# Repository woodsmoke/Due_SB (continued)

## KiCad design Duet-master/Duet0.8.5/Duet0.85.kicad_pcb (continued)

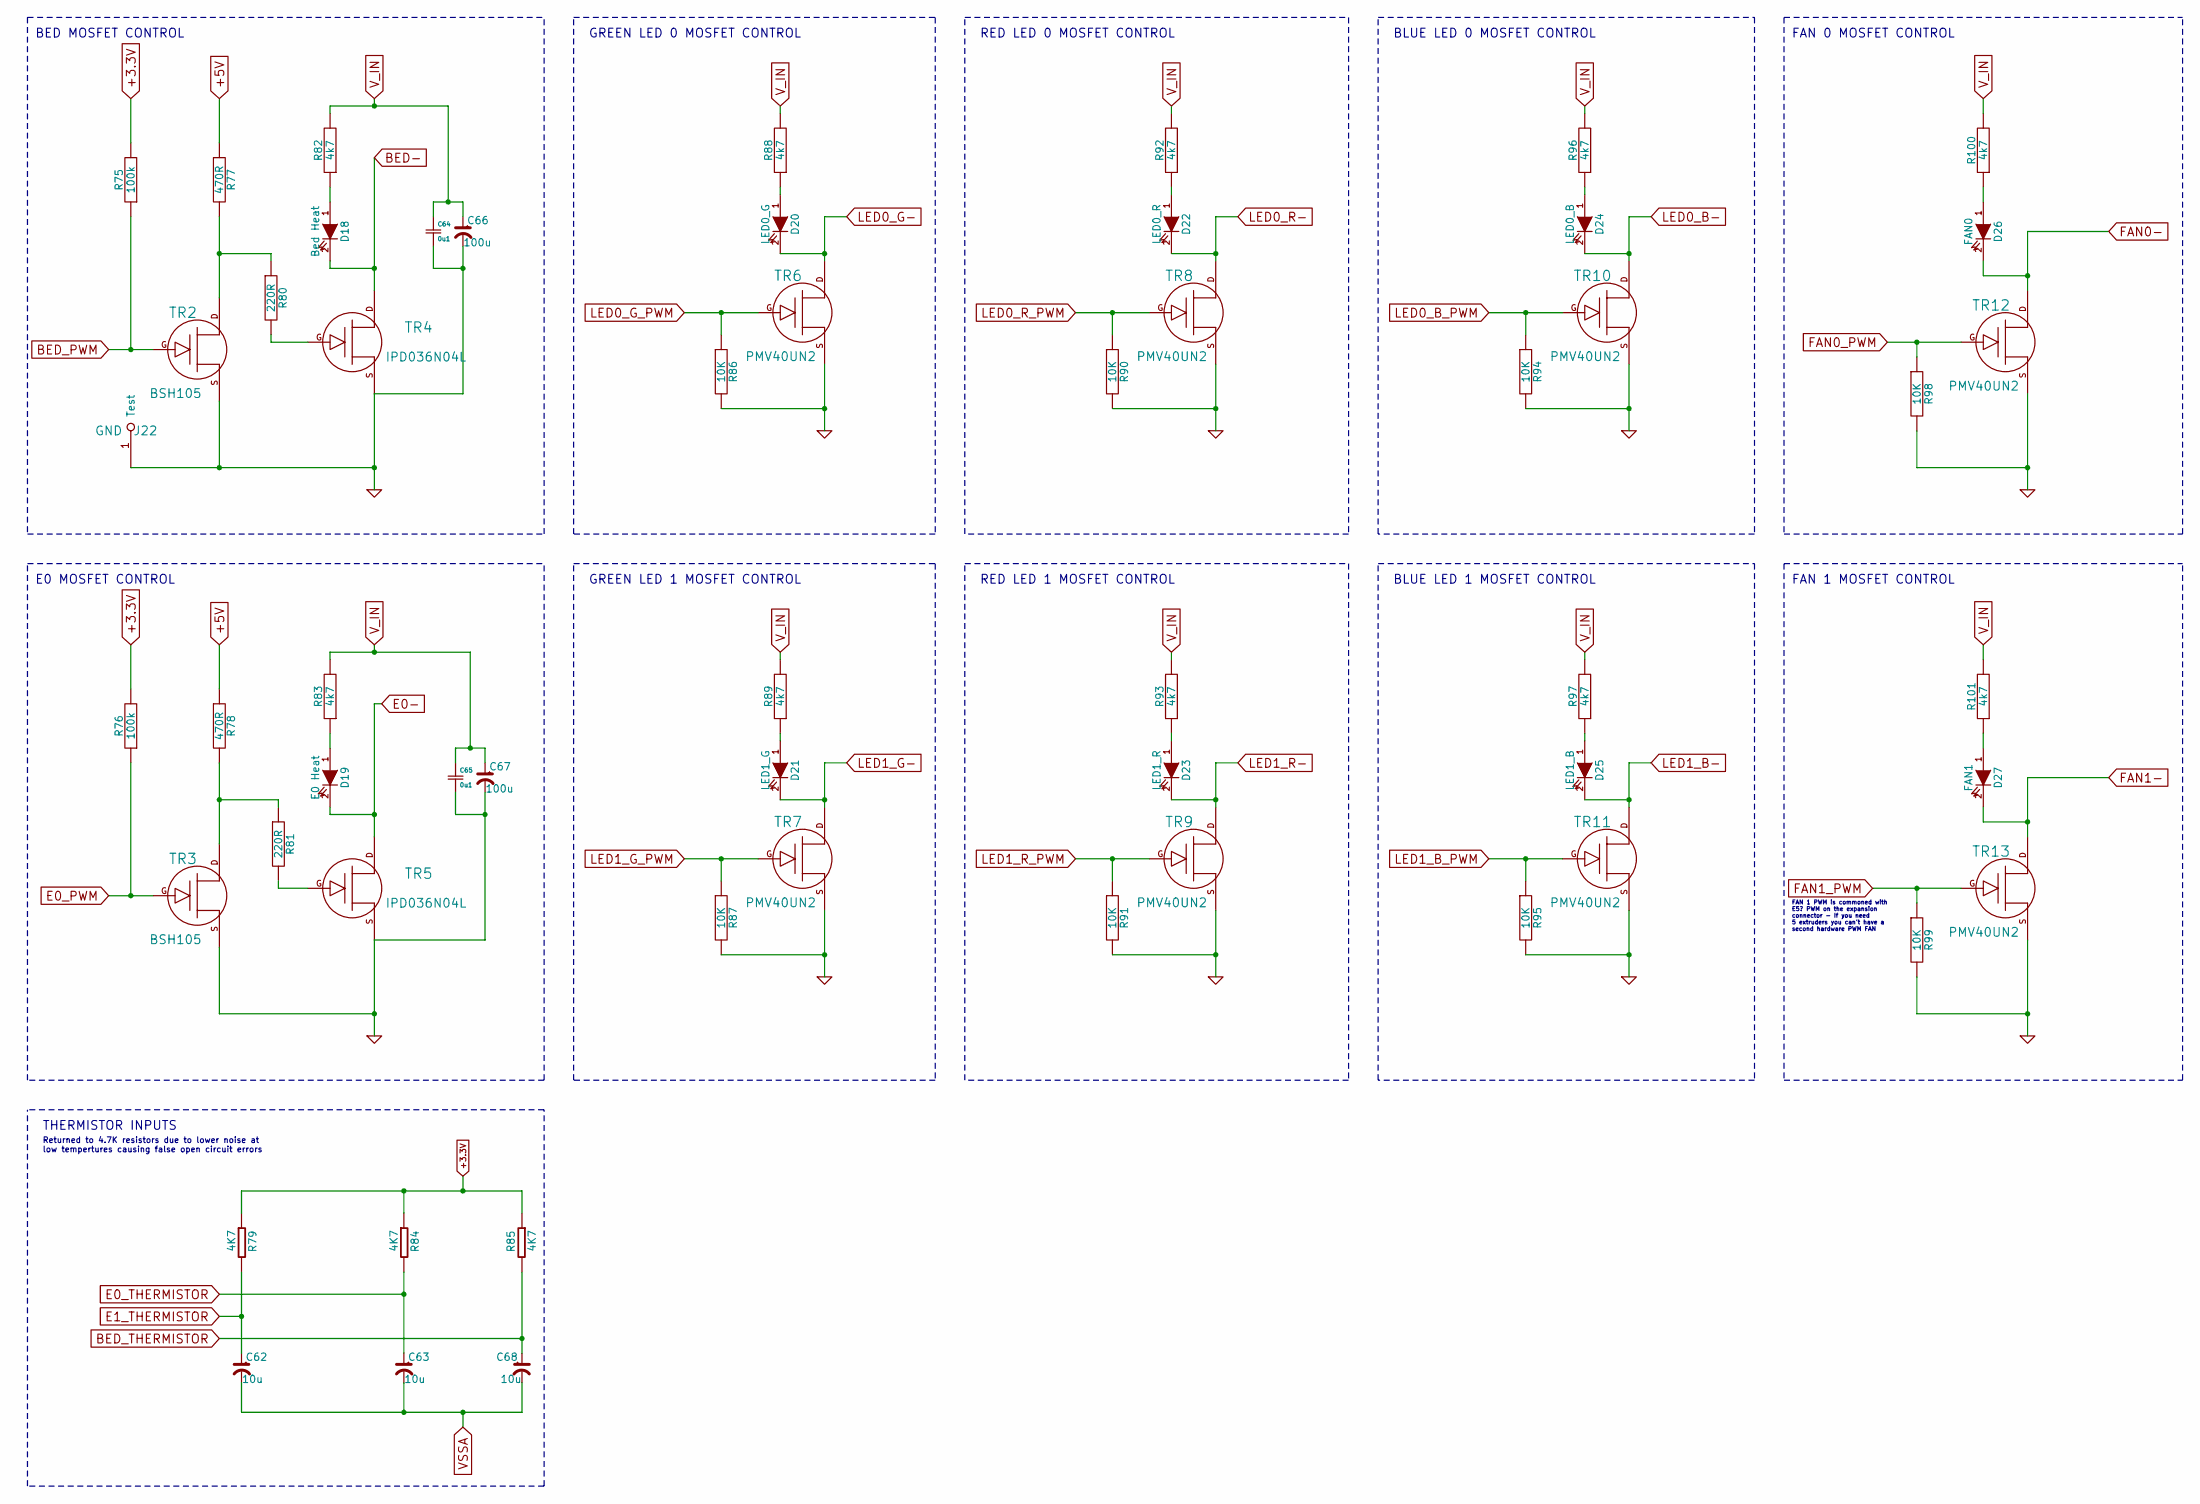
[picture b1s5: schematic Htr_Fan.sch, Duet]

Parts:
C62, C63, C68: 10u; 10mf_capacitor
C64, C65: 0u1; 0mf1_capacitor
C66, C67: 100u; 100mf_capacitor
D18: Bed Heat; BED_Diode_0603
D19: E0 Heat; E0_Diode_0603
D20: LED0_G; LED0_diode
D21: LED1_G; LED0_diode
D22: LED0_R; LED0_diode
D23: LED1_R; LED0_diode
D24: LED0_B; LED0_diode
D25: LED1_B; LED0_diode
D26: FAN0; FAN0_diode
D27: FAN1; FAN1_diode
J22: GND; GND_TP
R75, R76: 100k; 100k_R_0603
R77, R78: 470R; 470R_R_0603
R79, R84, R85: 4K7; 4k7_R_0603
R80, R81: 220R; 220R_R_0603
R82, R83, R88, R89, R92, R93, R96, R97, R100, R101: 4k7; 4k7_R_0603
R86, R87, R90, R91, R94, R95, R98, R99: 10K; 10k_R_0603
TR2, TR3: BSH105; BSH105_SOT-23
TR4, TR5: IPD036N04L; IPD036N04L_D-PAK
TR6, TR7, TR8, TR9, TR10, TR11, TR12, TR13: PMV40UN2; PMV40UN2_SOT-23

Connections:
+3.3V: R75.2, R76.2, R79.1, R84.1, R85.1; also elsewhere on the board
+5V: R77.1, R78.1; also elsewhere on the board
BED-: D18.2 (K), TR4.D; also elsewhere on the board
BED_PWM: R75.1, TR2.G; also elsewhere on the board
BED_THERMISTOR: C68.1, R85.2; also elsewhere on the board
E0-: D19.2 (K), TR5.D; also elsewhere on the board
E0_PWM: R76.1, TR3.G; also elsewhere on the board
E0_THERMISTOR: C63.1, R84.2; also elsewhere on the board
E1_THERMISTOR: C62.1, R79.2; also elsewhere on the board
FAN0-: D26.2 (K), TR12.D; also elsewhere on the board
FAN0_PWM: R98.1, TR12.G; also elsewhere on the board
FAN1-: D27.2 (K), TR13.D; also elsewhere on the board
FAN1_PWM: R99.1, TR13.G; also elsewhere on the board
GND: C64.2, C65.2, C66.2, C67.2, J22.1, R86.2, R87.2, R90.2, R91.2, R94.2, R95.2, R98.2, R99.2, TR2.S, TR3.S, TR4.S, TR5.S, TR6.S, TR7.S, TR8.S, TR9.S, TR10.S, TR11.S, TR12.S, TR13.S; also elsewhere on the board
LED0_B-: D24.2 (K), TR10.D; also elsewhere on the board
LED0_G-: D20.2 (K), TR6.D; also elsewhere on the board
LED0_R-: D22.2 (K), TR8.D; also elsewhere on the board
LED1_B-: D25.2 (K), TR11.D; also elsewhere on the board
LED1_G-: D21.2 (K), TR7.D; also elsewhere on the board
LED1_R-: D23.2 (K), TR9.D; also elsewhere on the board
unnamed: D18.1 (A), R82.1
unnamed: D19.1 (A), R83.1
unnamed: D20.1 (A), R88.1
unnamed: D21.1 (A), R89.1
unnamed: D22.1 (A), R92.1
unnamed: D23.1 (A), R93.1
unnamed: D24.1 (A), R96.1
unnamed: D25.1 (A), R97.1
unnamed: D26.1 (A), R100.1
unnamed: D27.1 (A), R101.1
unnamed: R77.2, R80.1, TR2.D
unnamed: R78.2, R81.1, TR3.D
unnamed: R80.2, TR4.G
unnamed: R81.2, TR5.G
VSSA: C62.2, C63.2, C68.2; also elsewhere on the board
V_IN: C64.1, C65.1, C66.1, C67.1, R82.2, R83.2, R88.2, R89.2, R92.2, R93.2, R96.2, R97.2, R100.2, R101.2; also elsewhere on the board

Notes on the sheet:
Returned to 4.7K resistors due to lower noise at low tempertures causing false open circuit errors
THERMISTOR INPUTS
FAN 0 MOSFET CONTROL
E0 MOSFET CONTROL
BED MOSFET CONTROL
FAN 1 MOSFET CONTROL
FAN 1 PWM is commoned with E5? PWM on the expansion connector - If you need 5 extruders you can't have a second hardware PWM FAN
RED LED 0 MOSFET CONTROL
GREEN LED 0 MOSFET CONTROL
BLUE LED 0 MOSFET CONTROL
RED LED 1 MOSFET CONTROL
GREEN LED 1 MOSFET CONTROL
BLUE LED 1 MOSFET CONTROL

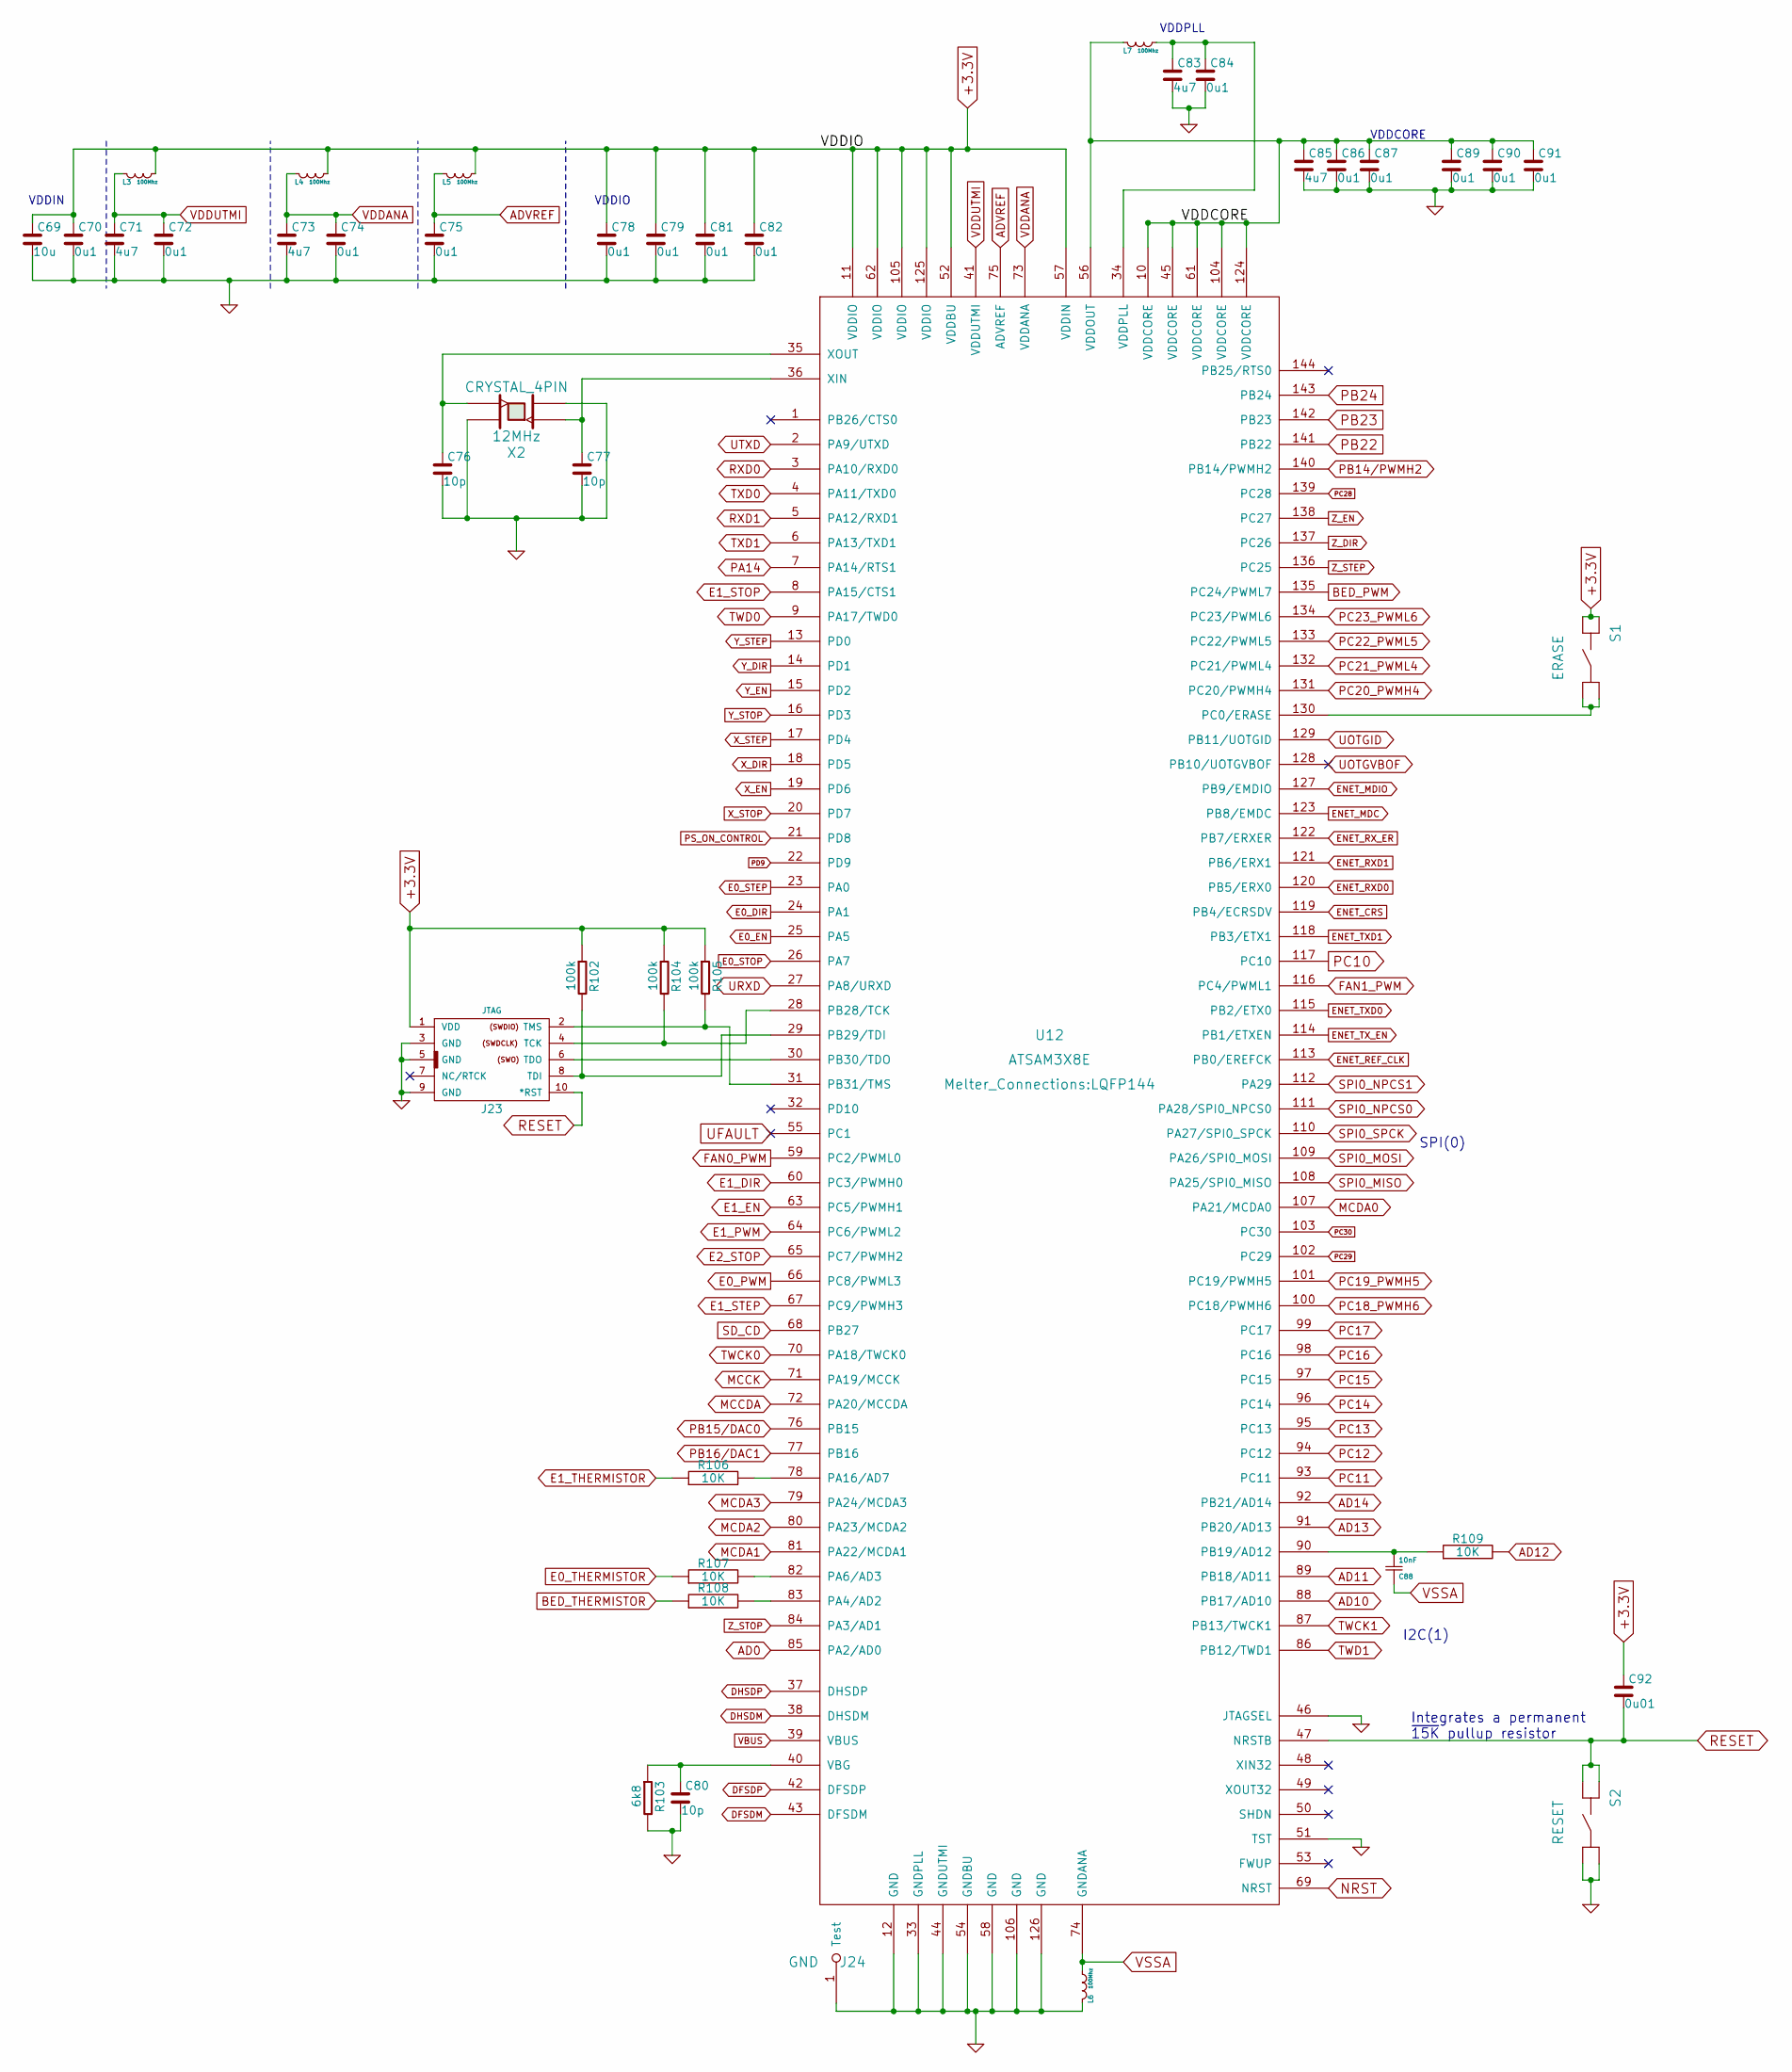
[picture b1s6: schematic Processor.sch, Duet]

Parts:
C69: 10u; 10mf_capacitor
C70, C72, C74, C75, C78, C79, C81, C82, C84, C86, C87, C89, C90, C91: 0u1; 0mf1_capacitor
C71, C73, C83, C85: 4u7; 4uf7_capacitor
C76, C77, C80: 10p; 10pf_capacitor
C88: 10nF; 10nf_capacitor
C92: 0u01; 0mf01_Capacitor
J23: JTAG; PIN_ARRAY_5x2
J24: GND; GND_TP
L3, L4, L5, L6, L7: 100Mhz; 100Mhz_R_0603
R102, R104, R105: 100k; 100k_R_0603
R103: 6k8; 6k8_R_0603
R106, R107, R108, R109: 10K; 10k_R_0603
S1: ERASE; SW_SIDE_1
S2: RESET; SW_SIDE_1
U12: ATSAM3X8E; LQFP144
X2: CRYSTAL_4PIN; Xtal_5x3.2

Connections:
+3.3V: C69.1, C70.1, C78.1, C79.1, C81.1, C82.1, C92.1, J23.1 (VDD), L3.2 (B), L4.2 (B), L5.2 (B), R102.1, R104.1, R105.1, S1.3, S1.4, U12.11 (VDDIO), U12.52 (VDDBU), U12.57 (VDDIN), U12.62 (VDDIO), U12.105 (VDDIO), U12.125 (VDDIO); also elsewhere on the board
/Processor/VDDCORE: C85.1, C86.1, C87.1, C89.1, C90.1, C91.1, L7.1 (A), U12.10 (VDDCORE), U12.45 (VDDCORE), U12.56 (VDDOUT), U12.61 (VDDCORE), U12.104 (VDDCORE), U12.124 (VDDCORE)
AD0: U12.85 (PA2/AD0); also elsewhere on the board
AD10: U12.88 (PB17/AD10); also elsewhere on the board
AD11: U12.89 (PB18/AD11); also elsewhere on the board
AD12: R109.2; also elsewhere on the board
AD13: U12.91 (PB20/AD13); also elsewhere on the board
AD14: U12.92 (PB21/AD14); also elsewhere on the board
ADVREF: C75.1, L5.1 (A), U12.75 (ADVREF)
BED_PWM: U12.135 (PC24/PWML7); also elsewhere on the board
BED_THERMISTOR: R108.1; also elsewhere on the board
DFSDM: U12.43 (DFSDM); also elsewhere on the board
DFSDP: U12.42 (DFSDP); also elsewhere on the board
DHSDM: U12.38 (DHSDM); also elsewhere on the board
DHSDP: U12.37 (DHSDP); also elsewhere on the board
E0_DIR: U12.24 (PA1); also elsewhere on the board
E0_EN: U12.25 (PA5); also elsewhere on the board
E0_PWM: U12.66 (PC8/PWML3); also elsewhere on the board
E0_STEP: U12.23 (PA0); also elsewhere on the board
E0_STOP: U12.26 (PA7); also elsewhere on the board
E0_THERMISTOR: R107.1; also elsewhere on the board
E1_DIR: U12.60 (PC3/PWMH0); also elsewhere on the board
E1_EN: U12.63 (PC5/PWMH1); also elsewhere on the board
E1_PWM: U12.64 (PC6/PWML2)
E1_STEP: U12.67 (PC9/PWMH3); also elsewhere on the board
E1_STOP: U12.8 (PA15/CTS1); also elsewhere on the board
E1_THERMISTOR: R106.1; also elsewhere on the board
E2_STOP: U12.65 (PC7/PWMH2); also elsewhere on the board
ENET_CRS: U12.119 (PB4/ECRSDV); also elsewhere on the board
ENET_MDC: U12.123 (PB8/EMDC); also elsewhere on the board
ENET_MDIO: U12.127 (PB9/EMDIO); also elsewhere on the board
ENET_REF_CLK: U12.113 (PB0/EREFCK); also elsewhere on the board
ENET_RXD0: U12.120 (PB5/ERX0); also elsewhere on the board
ENET_RXD1: U12.121 (PB6/ERX1); also elsewhere on the board
ENET_RX_ER: U12.122 (PB7/ERXER); also elsewhere on the board
ENET_TXD0: U12.115 (PB2/ETX0); also elsewhere on the board
ENET_TXD1: U12.118 (PB3/ETX1); also elsewhere on the board
ENET_TX_EN: U12.114 (PB1/ETXEN); also elsewhere on the board
FAN0_PWM: U12.59 (PC2/PWML0); also elsewhere on the board
FAN1_PWM: U12.116 (PC4/PWML1); also elsewhere on the board
GND: C69.2, C70.2, C71.2, C72.2, C73.2, C74.2, C75.2, C76.2, C77.2, C78.2, C79.2, C80.2, C81.2, C82.2, C83.2, C84.2, C85.2, C86.2, C87.2, C89.2, C90.2, C91.2, J23.3 (GND), J23.5 (GND), J23.9 (GND), J24.1, L6.1 (A), R103.2, S2.1, S2.2, U12.12 (GND), U12.33 (GNDPLL), U12.44 (GNDUTMI), U12.46 (JTAGSEL), U12.51 (TST), U12.54 (GNDBU), U12.58 (GND), U12.106 (GND), U12.126 (GND), X2.2, X2.4; also elsewhere on the board
MCCDA: U12.72 (PA20/MCCDA); also elsewhere on the board
MCCK: U12.71 (PA19/MCCK); also elsewhere on the board
MCDA0: U12.107 (PA21/MCDA0); also elsewhere on the board
MCDA1: U12.81 (PA22/MCDA1); also elsewhere on the board
MCDA2: U12.80 (PA23/MCDA2); also elsewhere on the board
MCDA3: U12.79 (PA24/MCDA3); also elsewhere on the board
NRST: U12.69 (NRST); also elsewhere on the board
unnamed: C76.1, U12.35 (XOUT), X2.3
unnamed: C77.1, U12.36 (XIN), X2.1
unnamed: C80.1, R103.1, U12.40 (VBG)
unnamed: C83.1, C84.1, L7.2 (B), U12.34 (VDDPLL)
unnamed: C88.2, R109.1, U12.90 (PB19/AD12)
unnamed: J23.2 (TMS), R105.2, U12.31 (PB31/TMS)
unnamed: J23.4 (TCK), R104.2, U12.28 (PB28/TCK)
unnamed: J23.6 (TDO), U12.30 (PB30/TDO)
unnamed: J23.8 (TDI), R102.2, U12.29 (PB29/TDI)
unnamed: R106.2, U12.78 (PA16/AD7)
unnamed: R107.2, U12.82 (PA6/AD3)
unnamed: R108.2, U12.83 (PA4/AD2)
unnamed: S1.1, S1.2, U12.130 (PC0/ERASE)
PA14: U12.7 (PA14/RTS1); also elsewhere on the board
PB14/PWMH2: U12.140 (PB14/PWMH2); also elsewhere on the board
PB15/DAC0: U12.76 (PB15); also elsewhere on the board
PB16/DAC1: U12.77 (PB16); also elsewhere on the board
PB22: U12.141 (PB22); also elsewhere on the board
PB23: U12.142 (PB23); also elsewhere on the board
PB24: U12.143 (PB24); also elsewhere on the board
PC10: U12.117 (PC10); also elsewhere on the board
PC11: U12.93 (PC11); also elsewhere on the board
PC12: U12.94 (PC12); also elsewhere on the board
PC13: U12.95 (PC13); also elsewhere on the board
PC14: U12.96 (PC14); also elsewhere on the board
PC15: U12.97 (PC15); also elsewhere on the board
PC16: U12.98 (PC16); also elsewhere on the board
PC17: U12.99 (PC17); also elsewhere on the board
PC28: U12.139 (PC28); also elsewhere on the board
PC29: U12.102 (PC29); also elsewhere on the board
PC30: U12.103 (PC30); also elsewhere on the board
PD9: U12.22 (PD9); also elsewhere on the board
PS_ON_CONTROL: U12.21 (PD8); also elsewhere on the board
RESET: C92.2, J23.10 (*RST), S2.3, S2.4, U12.47 (NRSTB); also elsewhere on the board
RXD0: U12.3 (PA10/RXD0); also elsewhere on the board
RXD1: U12.5 (PA12/RXD1); also elsewhere on the board
SD_CD: U12.68 (PB27); also elsewhere on the board
SPI0_MISO: U12.108 (PA25/SPI0_MISO); also elsewhere on the board
SPI0_MOSI: U12.109 (PA26/SPI0_MOSI); also elsewhere on the board
SPI0_NPCS0: U12.111 (PA28/SPI0_NPCS0); also elsewhere on the board
SPI0_NPCS1: U12.112 (PA29); also elsewhere on the board
SPI0_SPCK: U12.110 (PA27/SPI0_SPCK); also elsewhere on the board
TWCK0: U12.70 (PA18/TWCK0); also elsewhere on the board
TWCK1: U12.87 (PB13/TWCK1); also elsewhere on the board
TWD0: U12.9 (PA17/TWD0); also elsewhere on the board
TWD1: U12.86 (PB12/TWD1); also elsewhere on the board
TXD0: U12.4 (PA11/TXD0); also elsewhere on the board
TXD1: U12.6 (PA13/TXD1); also elsewhere on the board
UFAULT: U12.55 (PC1)
UOTGID: U12.129 (PB11/UOTGID); also elsewhere on the board
UOTGVBOF: U12.128 (PB10/UOTGVBOF)
URXD: U12.27 (PA8/URXD); also elsewhere on the board
UTXD: U12.2 (PA9/UTXD); also elsewhere on the board
VBUS: U12.39 (VBUS); also elsewhere on the board
VDDANA: C73.1, C74.1, L4.1 (A), U12.73 (VDDANA)
VDDUTMI: C71.1, C72.1, L3.1 (A), U12.41 (VDDUTMI)
VSSA: C88.1, L6.2 (B), U12.74 (GNDANA); also elsewhere on the board
X_DIR: U12.18 (PD5); also elsewhere on the board
X_EN: U12.19 (PD6); also elsewhere on the board
X_STEP: U12.17 (PD4); also elsewhere on the board
X_STOP: U12.20 (PD7); also elsewhere on the board
Y_DIR: U12.14 (PD1); also elsewhere on the board
Y_EN: U12.15 (PD2); also elsewhere on the board
Y_STEP: U12.13 (PD0); also elsewhere on the board
Y_STOP: U12.16 (PD3); also elsewhere on the board
Z_DIR: U12.137 (PC26); also elsewhere on the board
Z_EN: U12.138 (PC27); also elsewhere on the board
Z_STEP: U12.136 (PC25); also elsewhere on the board
Z_STOP: U12.84 (PA3/AD1); also elsewhere on the board

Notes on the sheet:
Integrates a permanent ~15K pullup resistor
SPI(0)
I2C(1)
VDDPLL
VDDCORE
VDDIO
VDDIN

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
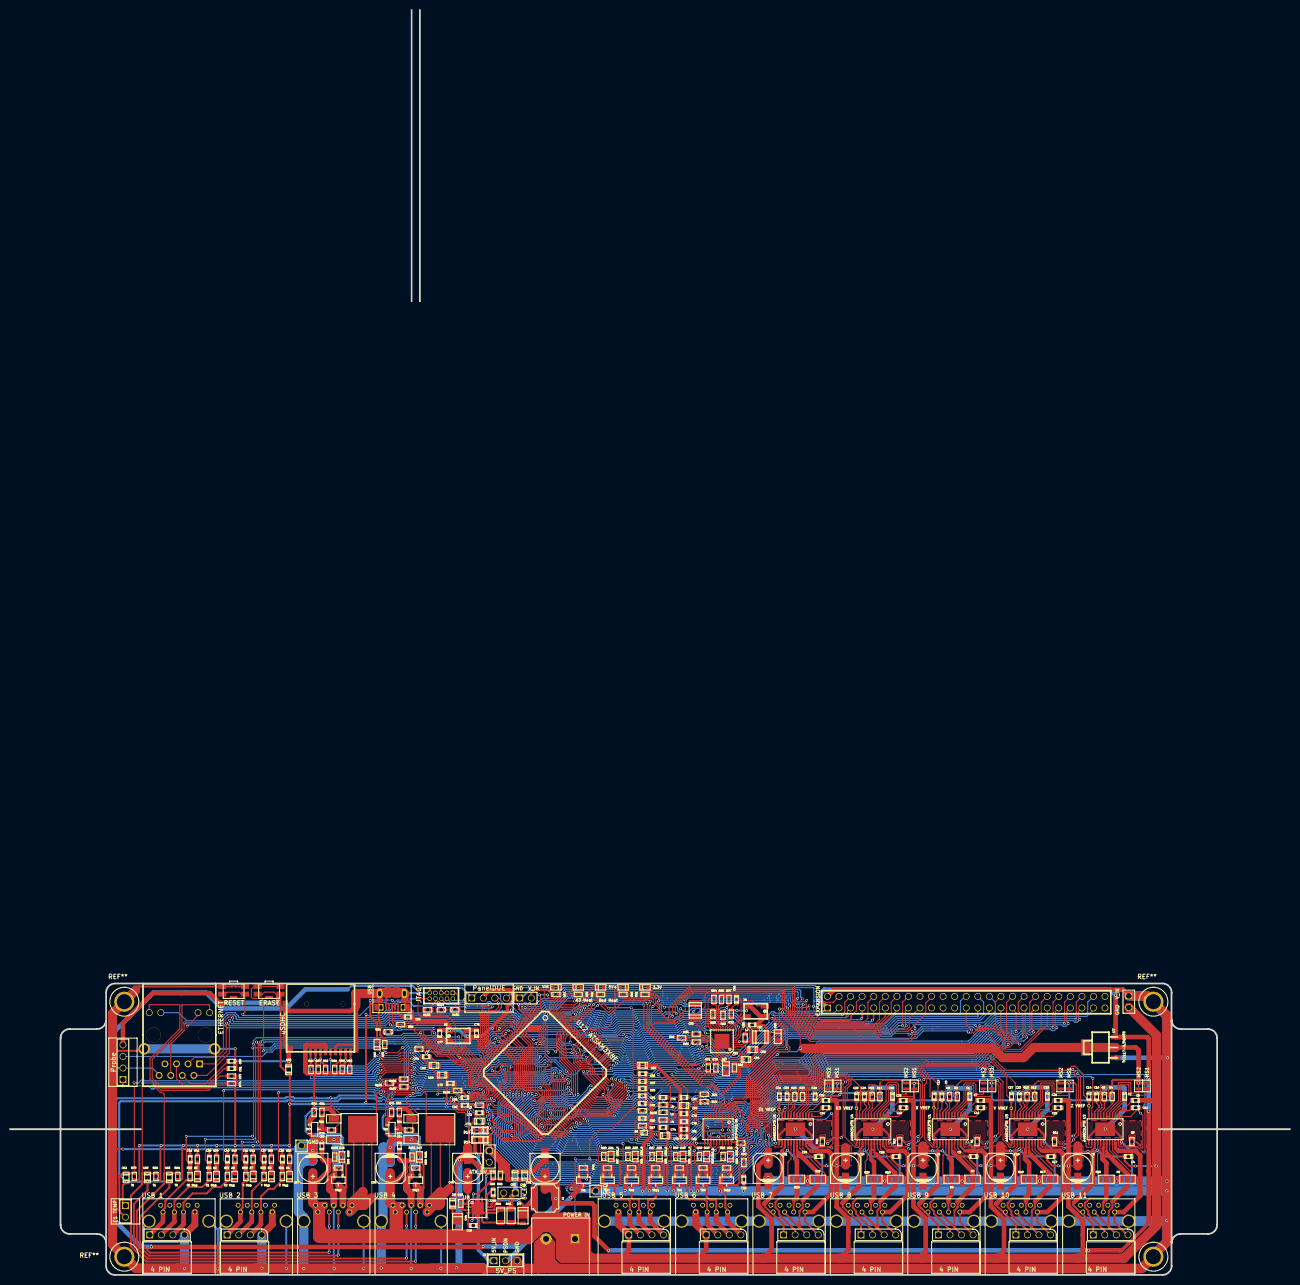
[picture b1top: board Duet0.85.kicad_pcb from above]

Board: 4 copper layers, 281.1 x 277.8 mm, 313 parts (0 on the bottom side), 265 nets.

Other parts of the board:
H1, H2, H3, H4, H5, H6, H7, H8, H9: 4 PIN; RA_PIN_ARRAY_4x1
USB 1: SENSE 2; USB_3
USB 2: SENSE 1; USB_3
USB 3: PWR/SENSE 1; USB_3
USB 4: PWR/SENSE 2; USB_3
USB 5: LIGHT 2; USB_3
USB 6: LIGHT 1; USB_3
USB 7: MOTOR 1; USB_3
USB 8: MOTOR 2; USB_3
USB 9: MOTOR 3; USB_3
USB 10: MOTOR 4; USB_3
USB 11: MOTOR 5; USB_3

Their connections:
BED-: USB 4.4, USB 4.5; also elsewhere on the board
BED_THERMISTOR: USB 4.3; also elsewhere on the board
E0-: USB 3.4, USB 3.5; also elsewhere on the board
E0_MOT_1A: H6.2, USB 8.3; also elsewhere on the board
E0_MOT_1B: H6.1, USB 8.1; also elsewhere on the board
E0_MOT_2A: H6.3, USB 8.2; also elsewhere on the board
E0_MOT_2B: H6.4, USB 8.4; also elsewhere on the board
E0_STOP_CONN: H1.1, USB 1.1; also elsewhere on the board
E0_THERMISTOR: USB 3.3; also elsewhere on the board
E1_MOT_1A: H5.2, USB 7.3; also elsewhere on the board
E1_MOT_1B: H5.1, USB 7.1; also elsewhere on the board
E1_MOT_2A: H5.3, USB 7.2; also elsewhere on the board
E1_MOT_2B: H5.4, USB 7.4; also elsewhere on the board
E1_STOP_CONN: H1.2, USB 1.2; also elsewhere on the board
E2_STOP_CONN: H1.3, USB 1.3; also elsewhere on the board
FAN0-: USB 3.6; also elsewhere on the board
FAN1-: USB 4.6; also elsewhere on the board
GND: H1.4, H2.4, USB 1.4, USB 1.10, USB 2.4, USB 2.10, USB 3.7, USB 3.10, USB 4.7, USB 4.10, USB 5.10, USB 6.10, USB 7.10, USB 8.10, USB 9.10, USB 10.10, USB 11.10; also elsewhere on the board
LED0_B-: H4.4, USB 6.4; also elsewhere on the board
LED0_G-: H4.2, USB 6.2; also elsewhere on the board
LED0_R-: H4.3, USB 6.3; also elsewhere on the board
LED1_B-: H3.4, USB 5.4; also elsewhere on the board
LED1_G-: H3.2, USB 5.2; also elsewhere on the board
LED1_R-: H3.3, USB 5.3; also elsewhere on the board
VSSA: USB 3.2, USB 4.2; also elsewhere on the board
V_IN: H3.1, H4.1, USB 3.1, USB 3.8, USB 3.9, USB 4.1, USB 4.8, USB 4.9, USB 5.1, USB 6.1; also elsewhere on the board
X_MOT_1A: H7.2, USB 9.3; also elsewhere on the board
X_MOT_1B: H7.1, USB 9.1; also elsewhere on the board
X_MOT_2A: H7.3, USB 9.2; also elsewhere on the board
X_MOT_2B: H7.4, USB 9.4; also elsewhere on the board
X_STOP_CONN: H2.1, USB 2.1; also elsewhere on the board
Y_MOT_1A: H8.2, USB 10.3; also elsewhere on the board
Y_MOT_1B: H8.1, USB 10.1; also elsewhere on the board
Y_MOT_2A: H8.3, USB 10.2; also elsewhere on the board
Y_MOT_2B: H8.4, USB 10.4; also elsewhere on the board
Y_STOP_CONN: H2.2, USB 2.2; also elsewhere on the board
Z_MOT_1A: H9.2, USB 11.3; also elsewhere on the board
Z_MOT_1B: H9.1, USB 11.1; also elsewhere on the board
Z_MOT_2A: H9.3, USB 11.2; also elsewhere on the board
Z_MOT_2B: H9.4, USB 11.4; also elsewhere on the board
Z_STOP_CONN: H2.3, USB 2.3; also elsewhere on the board

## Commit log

2015-08-09 :octocat: Added .gitattributes & .gitignore files
2015-08-09 File upload
    First commit
2015-08-09 USB Receptacle Footprints
    KiCad Footprints for USB 2.0/3.0 receptacles
2015-08-10 Module Library update
    Lots of duplicate footprints
2015-08-12 PCB layout of components started
    Experienced advice welcome.
2015-08-13 Finalising draft layout for comment
2015-08-13 Finalising first draft layout for comment
2015-08-14 USB 3 receptacles!
2015-08-15 0.1" headers added
2015-08-15 Routing started
2015-08-17 More routing, even under crystals.
2015-08-18 More routing
2015-08-19 Nearly complete
2015-08-21 Clean up
2015-08-21 Cleaned
2015-08-22 Some GND connections beefed up
